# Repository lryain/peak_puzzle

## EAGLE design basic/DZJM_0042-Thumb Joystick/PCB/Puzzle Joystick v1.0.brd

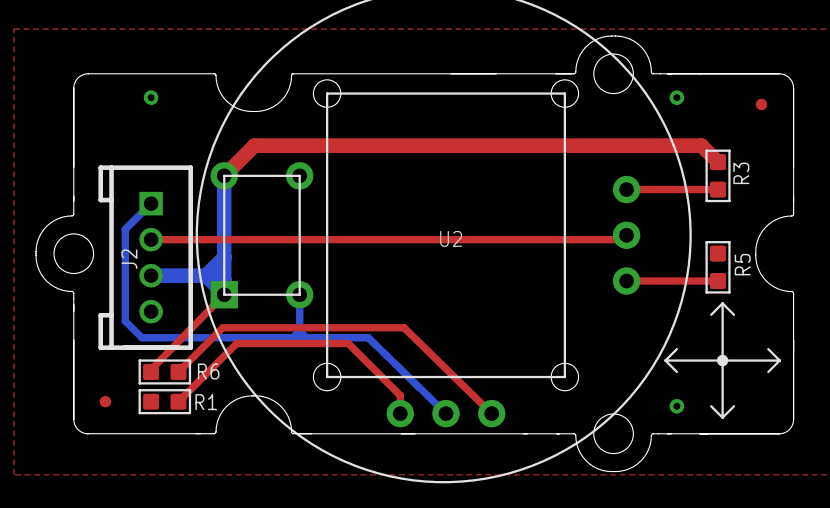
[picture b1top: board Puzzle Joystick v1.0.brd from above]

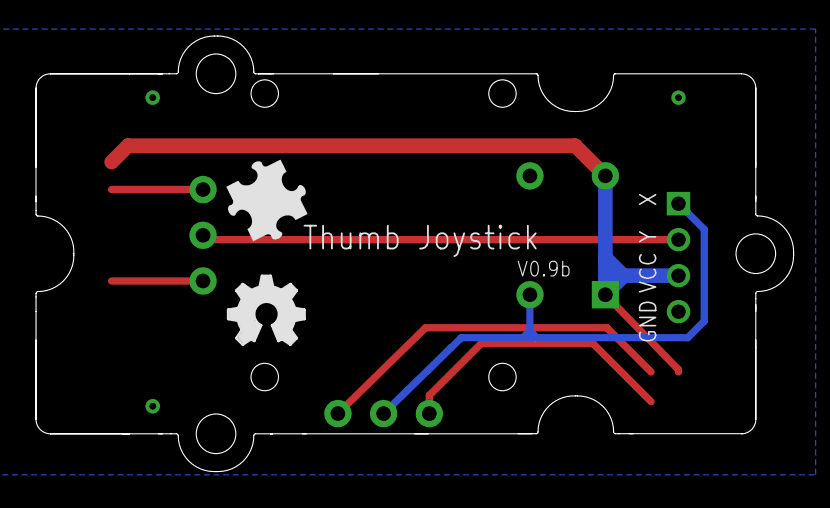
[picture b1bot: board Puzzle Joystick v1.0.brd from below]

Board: 2 copper layers, 42.1 x 24.2 mm, 11 parts (2 on the bottom side), 8 nets.

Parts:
J2: 4P-LEADED-2.0
LOGO1: LOGO-OSHW-FILLX0150-NT; OSHW_FILLX150_NOTEXT
MARK1, MARK2: PAD-MARK; MARK
R1, R5, R6: 4.7k; 0603
R3: 10R; 0603
U2: PSROCKER
U3: 2U-DIM-W/-DRILL
U$1: BRICK-LOGO-MIL-0.5

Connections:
GND: J2.4, R1.2, R5.2
unnamed: R3.2, U2.C2
unnamed: R6.2, U2.D2
unnamed: R1.1, U2.D0
unnamed: R5.1, U2.C0
OUT_X: J2.1, U2.B1, U2.D1
OUT_Y: J2.2, U2.C1
VCC: J2.3, R3.1, R6.1, U2.A1, U2.A2

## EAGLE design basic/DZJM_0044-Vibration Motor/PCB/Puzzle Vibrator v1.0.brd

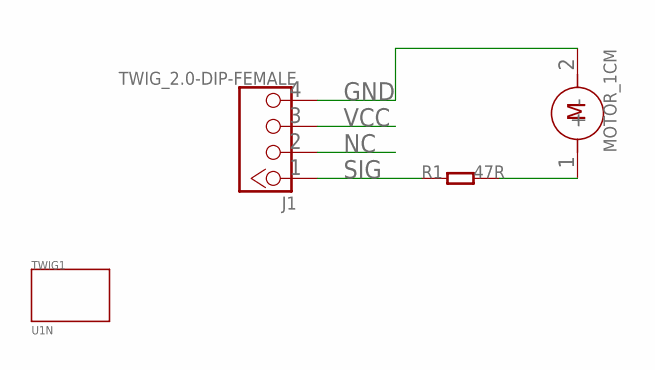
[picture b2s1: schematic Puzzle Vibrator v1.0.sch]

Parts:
J1: TWIG_2.0-DIP-FEMALE; 2.0_1X4
M1: MOTOR_1CM
R1: 47R; 0603_S
TWIG1: U1N

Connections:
GND: J1.4, M1.2 (-)
unnamed: M1.1 (+), R1.2
NC: J1.2
SIG: J1.1, R1.1
VCC: J1.3

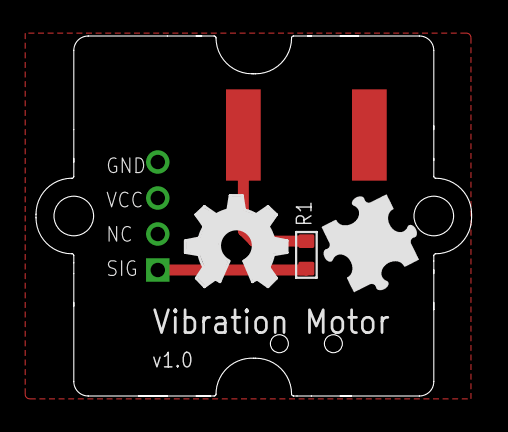
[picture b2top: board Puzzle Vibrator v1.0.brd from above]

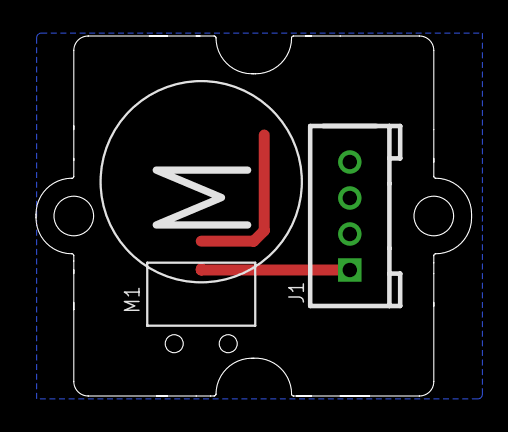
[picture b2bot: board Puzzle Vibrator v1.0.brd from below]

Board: 2 copper layers, 24.2 x 20.0 mm, 6 parts (3 on the bottom side), 3 nets.

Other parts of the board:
U$1: BRICK-LOGO-MIL-0.6
U$2: OSHW_FILLX200_NOTEXT
